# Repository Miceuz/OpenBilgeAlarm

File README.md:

# OpenBilgeAlarm
An open source bilge water level alarm system 

## Requirements

It is important to comply with the regulations in SOLAS (International Convention for the Safety of Life at Sea), which means:

1. visual and audible alarm if bilges submerge with water
2. permanent check of the whole system and alert if sensor or wiring fails

### Environment

The system will work under moist conditions. The microcontroller can be located in the navigation room. Simple protection against dust and moisture will be sufficient. It is a dry and warm space. No need for any special casing. I would try to make it as a panel to be integrated into the board of all the other technical devices there. Ambient T is 10°C to 30°C. Humidity is rather high. Shock is low but may occur if some part may break and move inside the bilge (that is why I suggest having a cage around the sensor. i'll try to make a sketch or picture). Corrosion is high.

### Wiring

For our ship. I would count 35-40 meters of the bus backbone to the furthest sensor. From the backbone each sensor will need about 6-8 meters of cable. We have a cable channel along the side wall of the ship, where it will run along. Since the deepest parts of the sections will always be near the section walls, the backbone will be intersected there with the T-connectors.
So the furthest sensor should have something like 45m cable at max.

### Power

The ship runs on 24V DC batteries, which are charged and maintained externally. There is also a 220V AC inverter, but I prefer using the 24V DC and have a little converter for our needs. The maximum voltage we may have to consider is 29V in cases of charging with the generator. The minimum can get as low as 22.5V in case we are running really low on voltage.

But having a backup-battery will be a good idea anyways in case anything goes wrong with the other supplies?

## System architecture

 * A network of sensors is deployed on RS485 transport
 * [RS485-based soil moisture sensor](https://github.com/Miceuz/rs485-moist-sensor) is used
 * Central control system with user interface

### User interface

 * 2x16 character LCD
 * Rotary encoder w push button
 * Bright red alarm led
 * Multicolor status led
 * Buzzer
 * "Silence" button

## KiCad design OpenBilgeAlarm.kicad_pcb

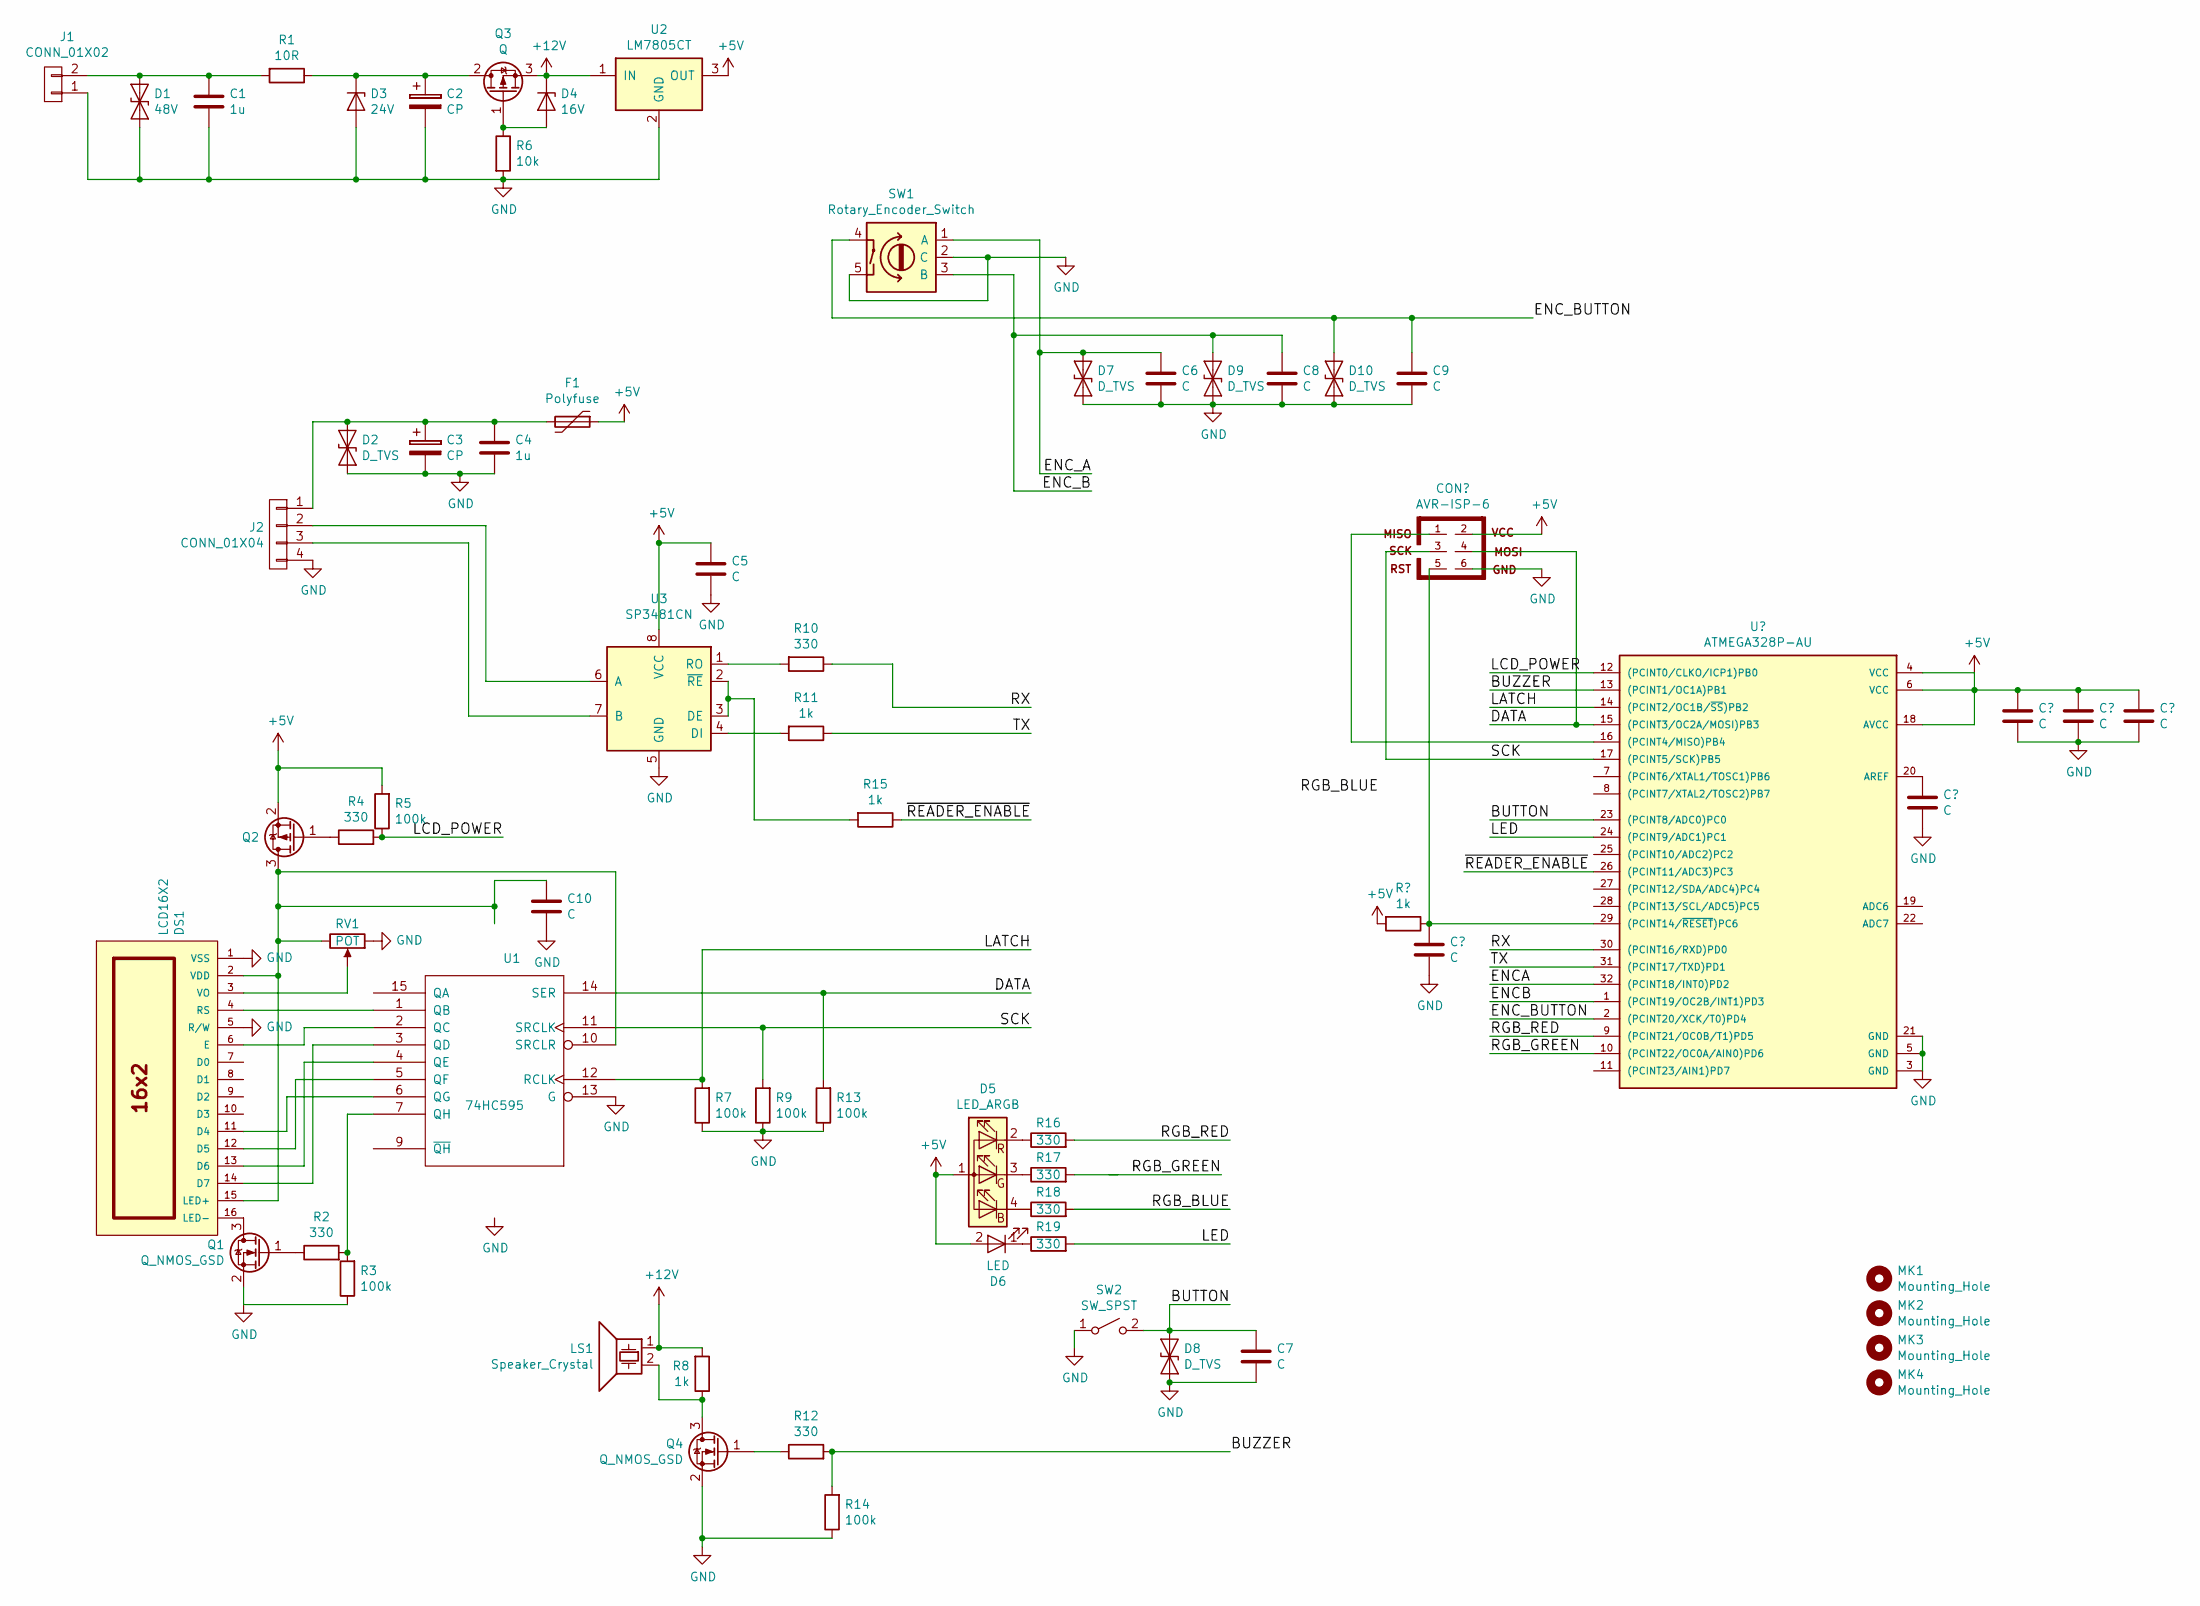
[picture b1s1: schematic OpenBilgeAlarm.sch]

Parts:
C1, C4: 1u; C_1210_HandSoldering; PartNo ?
C2, C3: CP; CP_Radial_D5.0mm_P2.50mm; PartNo ?
C5, C6, C7, C8, C9, C10: C; C_0603_HandSoldering; PartNo ?
D1: 48V; Diode-SMB_Handsoldering; PartNo SMBJ30CA
D2, D7, D8, D9, D10: D_TVS; SOD-323; PartNo ?
D3: 24V; Diode-SMA_Handsoldering; PartNo 1SMA5934BT3G
D4: 16V; D_SOD-323_HandSoldering; PartNo MM3Z16VST1G
D5: LED_ARGB; LED_D5.0mm-4; PartNo ?
D6: LED; LED_D5.0mm; PartNo ?
DS1: LCD16X2; WC1602A; PartNo ?
F1: Polyfuse; R_Box_L8.4mm_W2.5mm_P5.08mm; PartNo ?
J1: CONN_01X02; TerminalBlock_5.08-2pol; PartNo ?
J2: CONN_01X04; TerminalBlock_5.08-5pol; PartNo ?
LS1: Speaker_Crystal; Buzzer_12x9.5RM7.6; PartNo ?
MK1, MK2, MK3, MK4: Mounting_Hole; MountingHole_3.2mm_M3; PartNo ?
Q1, Q4: Q_NMOS_GSD; SOT-23_Handsoldering; PartNo ?
Q2: Q_PMOS_GSD; SOT-23_Handsoldering; PartNo ?
Q3: Q; TO-252-2Lead; PartNo IRFR5410TRPBF
R1: 10R; R_2512; PartNo ?
R2, R4, R10, R12, R16, R17, R18, R19: 330; R_0603_HandSoldering; PartNo ?
R3, R5, R7, R9, R13, R14: 100k; R_0603_HandSoldering; PartNo ?
R6: 10k; R_0603_HandSoldering; PartNo ?
R8, R11, R15: 1k; R_0603_HandSoldering; PartNo ?
RV1: POT; Potentiometer_Trimmer_ACP_CA6v_Horizontal; PartNo ?
SW1: Rotary_Encoder_Switch; Encoder_Bourns_PEC12R-4xxxF-Sxxxx; PartNo ?
SW2: SW_SPST; SW_SPST_EVPBF; PartNo ?
U1: 74HC595; SOIC-16_3.9x9.9mm_Pitch1.27mm; PartNo ?
U2: LM7805CT; TO-220_Vertical
U3: SP3481CN; SOIC-8_3.9x4.9mm_Pitch1.27mm

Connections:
+5V: C5.1, D5.1 (A), D6.2 (A), F1.1, Q2.2 (S), R5.2, U2.3 (OUT), U3.8 (VCC); also elsewhere on the board
+12V: D4.1 (K), LS1.1, Q3.3 (S), R8.2, U2.1 (IN)
/BUTTON: C7.1, D8.1 (A1), SW2.2 (B); also elsewhere on the board
/BUZZER: R12.2, R14.2; also elsewhere on the board
/DATA: R13.2, U1.14 (SER); also elsewhere on the board
/ENC_A: C6.1, D7.1 (A1), SW1.1 (A); also elsewhere on the board
/ENC_B: C8.1, D9.1 (A1), SW1.3 (B); also elsewhere on the board
/ENC_BUTTON: C9.1, D10.1 (A1), SW1.4; also elsewhere on the board
/LATCH: R7.2, U1.12 (RCLK); also elsewhere on the board
/LCD_POWER: R4.2, R5.1; also elsewhere on the board
/LED: R19.2; also elsewhere on the board
/RGB_BLUE: R18.2; also elsewhere on the board
/RGB_GREEN: R17.2; also elsewhere on the board
/RGB_RED: R16.2; also elsewhere on the board
/RX: R10.1; also elsewhere on the board
/SCK: R9.2, U1.11 (SRCLK); also elsewhere on the board
/TX: R11.1; also elsewhere on the board
/~READER_ENABLE: R15.1; also elsewhere on the board
GND: C1.2, C2.2, C3.2, C4.2, C5.2, C6.2, C7.2, C8.2, C9.2, C10.2, D1.2 (A2), D2.2 (A2), D3.2 (A), D7.2 (A2), D8.2 (A2), D9.2 (A2), D10.2 (A2), DS1.1 (VSS), DS1.5 (R/W), J1.1, J2.4, Q1.2 (S), Q4.2 (S), R3.1, R6.2, R7.1, R9.1, R13.1, R14.1, RV1.1, SW1.2 (C), SW1.5, SW2.1 (A), U1.8 (GND), U1.13 (G), U2.2 (GND), U3.5 (GND); also elsewhere on the board
unnamed: C1.1, D1.1 (A1), J1.2, R1.2
unnamed: C2.1, D3.1 (K), Q3.2 (D), R1.1
unnamed: C3.1, C4.1, D2.1 (A1), F1.2, J2.1
unnamed: D4.2 (A), Q3.1 (G), R6.1
unnamed: D5.2 (RK), R16.1
unnamed: D5.3 (GK), R17.1
unnamed: D5.4 (BK), R18.1
unnamed: D6.1 (K), R19.1
unnamed: DS1.3 (VO), RV1.2
unnamed: DS1.4 (RS), U1.1 (QB)
unnamed: DS1.6 (E), U1.2 (QC)
unnamed: DS1.11 (D4), U1.6 (QG)
unnamed: DS1.12 (D5), U1.5 (QF)
unnamed: DS1.13 (D6), U1.4 (QE)
unnamed: DS1.14 (D7), U1.3 (QD)
unnamed: DS1.16 (LED-), Q1.3 (D)
unnamed: J2.2, U3.6 (A)
unnamed: J2.3, U3.7 (B)
unnamed: LS1.2, Q4.3 (D), R8.1
unnamed: Q1.1 (G), R2.1
unnamed: Q2.1 (G), R4.1
unnamed: Q4.1 (G), R12.1
unnamed: R2.2, R3.2, U1.7 (QH)
unnamed: R10.2, U3.1 (RO)
unnamed: R11.2, U3.4 (DI)
unnamed: R15.2, U3.2 (~RE~), U3.3 (DE)

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
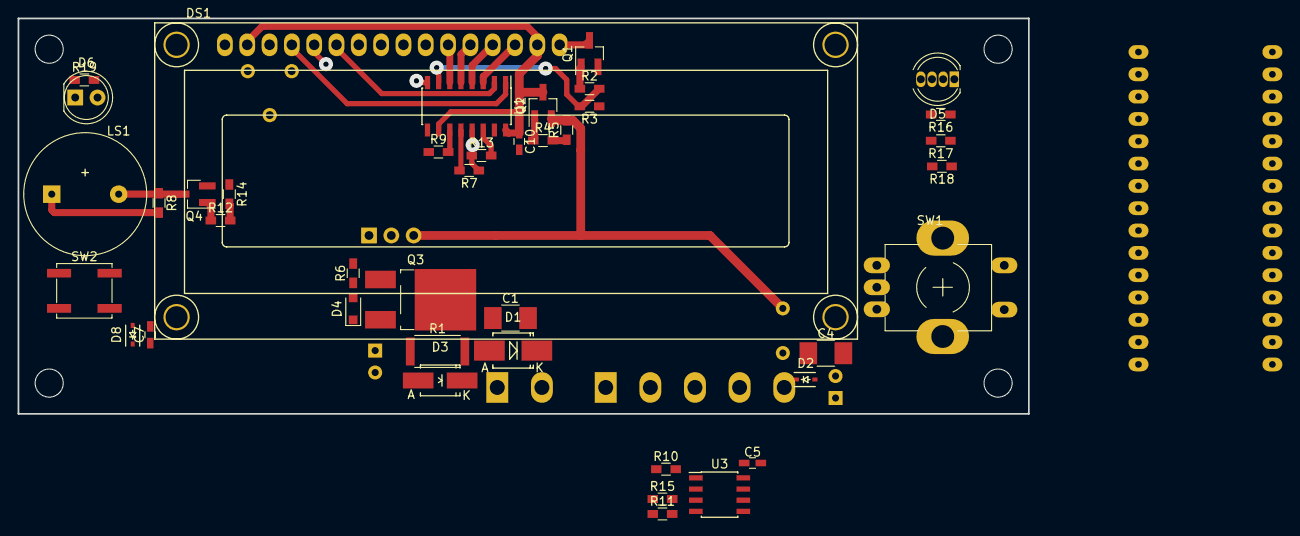
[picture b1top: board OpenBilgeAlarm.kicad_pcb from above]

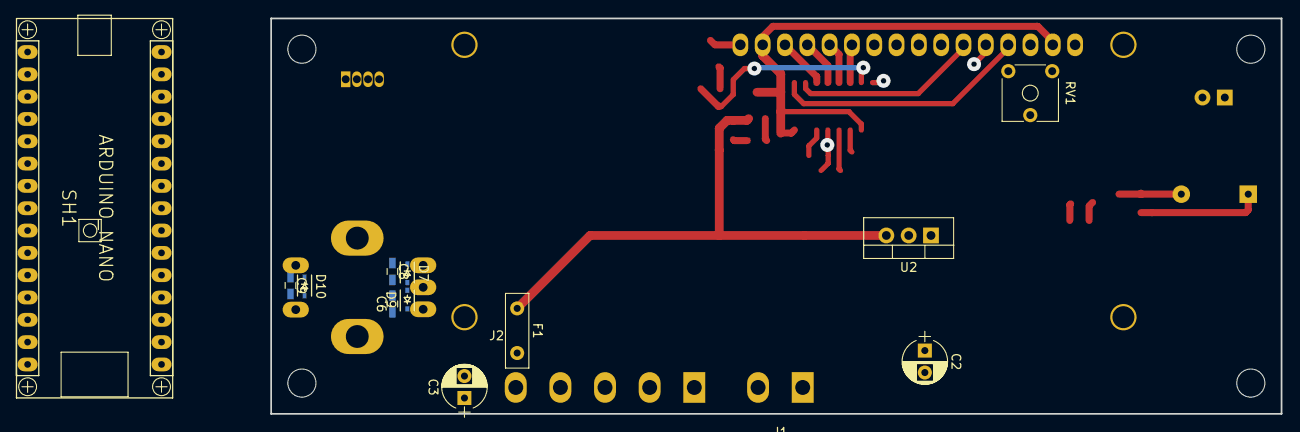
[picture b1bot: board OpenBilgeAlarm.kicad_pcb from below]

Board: 2 copper layers, 115.0 x 45.0 mm, 59 parts (14 on the bottom side), 46 nets.

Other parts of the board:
SH1: ARDUINO_NANO; ARDUINO_NANO_2_CONTOUR_ELL

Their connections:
+5V: SH1.5V; also elsewhere on the board
/BUTTON: SH1.7; also elsewhere on the board
/BUZZER: SH1.9; also elsewhere on the board
/DATA: SH1.12; also elsewhere on the board
/ENC_A: SH1.2; also elsewhere on the board
/ENC_B: SH1.3; also elsewhere on the board
/ENC_BUTTON: SH1.A0; also elsewhere on the board
/LATCH: SH1.10; also elsewhere on the board
/LCD_POWER: SH1.A1; also elsewhere on the board
/LED: SH1.8; also elsewhere on the board
/RGB_BLUE: SH1.11; also elsewhere on the board
/RGB_GREEN: SH1.6; also elsewhere on the board
/RGB_RED: SH1.5; also elsewhere on the board
/RX: SH1.0; also elsewhere on the board
/SCK: SH1.13; also elsewhere on the board
/TX: SH1.1; also elsewhere on the board
/~READER_ENABLE: SH1.4; also elsewhere on the board
GND: SH1.GND1, SH1.GND2; also elsewhere on the board

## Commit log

2017-04-10 Add rough and ready requirement description
2017-04-10 Add some basic ramblings about system architecture
2017-04-10 Throw some components to the schematic
2017-04-13 More or less finished schematics, some stuff left to source
2017-04-19 Start an expenses file
2017-04-19 Throw everything on board, try to route, start solving the mechanical puzzle
